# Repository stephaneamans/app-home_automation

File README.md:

# Home automation

## General principle

The general principle is based on a centralised ECU (Raspbery Pi) with an optional coprpocessor (STM32) used to manage low speed IO.
It shall communicate with satellite modules dedicated to specific tasks (like input, output and so on).

The main ECU shall communicate with an high speed link (Ethernet / WiFi) to the gateway.
A communication link shall be established with the satellite modules even by wire (RS-485) or wireless (NRF24L01, 2.4 gHz link).

The system is based on a Home Assistant server able to centralize different variables (temperature, lightining, ...),
commands (switch light on or off, enable a swimming pool filter, ...) or video streams (IP camera).
This server allows the system administrator to manage the system with a local computer and
users to interact with it through terminals (smartphone based, iOS or Android).

[Rapberry pi motherboard documentation](./01-raspberry_pi_motherboard/01-documentation/raspberry_pi_motherboard.md)

[Satellite module documentation](./02-module_satellite/01-documentation/module.md)

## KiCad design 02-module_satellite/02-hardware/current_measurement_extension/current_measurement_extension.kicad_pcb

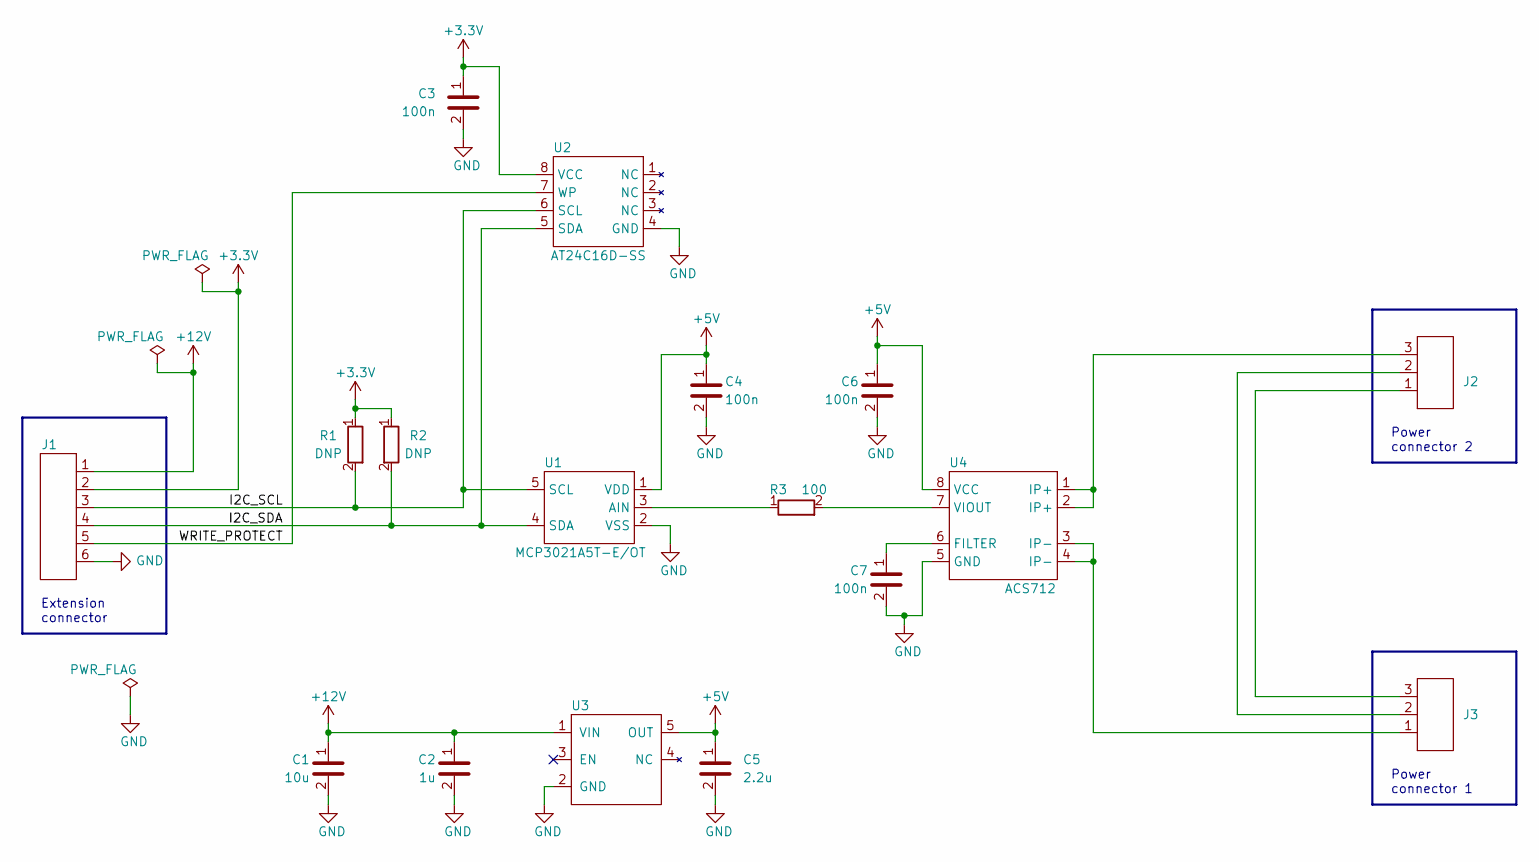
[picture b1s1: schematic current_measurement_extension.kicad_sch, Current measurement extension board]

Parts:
C1: 10u; C_1206_3216Metric_Pad1.33x1.80mm_HandSolder
C2: 1u; C_0603_1608Metric_Pad1.08x0.95mm_HandSolder
C3, C4, C6, C7: 100n; C_0603_1608Metric_Pad1.08x0.95mm_HandSolder
C5: 2.2u; C_0603_1608Metric_Pad1.08x0.95mm_HandSolder
J1: Conn_HE13_1x6_2.54V; PinHeader_1x06_P2.54mm_Vertical
J2, J3: Conn_HE13_1x3_2.54V; PinHeader_1x03_P2.54mm_Vertical
R1, R2: DNP; R_0603_1608Metric_Pad0.98x0.95mm_HandSolder
R3: 100; R_0603_1608Metric_Pad0.98x0.95mm_HandSolder
U1: MCP3021A5T-E/OT; SOT-23-5
U2: AT24C16D-SS; SOIC-8_3.9x4.9mm_P1.27mm
U3: TPS70950DBV; SOT-23-5
U4: ACS712; SOIC-8_3.9x4.9mm_P1.27mm

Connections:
+3.3V: C3.1, J1.2, R1.1, R2.1, U2.8 (VCC)
+5V: C4.1, C5.1, C6.1, U1.1 (VDD), U3.5 (OUT), U4.8 (VCC)
+12V: C1.1, C2.1, J1.1, U3.1 (VIN)
/I2C_SCL: J1.3, R1.2, U1.5 (SCL), U2.6 (SCL)
/I2C_SDA: J1.4, R2.2, U1.4 (SDA), U2.5 (SDA)
/WRITE_PROTECT: J1.5, U2.7 (WP)
GND: C1.2, C2.2, C3.2, C4.2, C5.2, C6.2, C7.2, J1.6, U1.2 (VSS), U2.4 (GND), U3.2 (GND), U4.5 (GND)
unnamed: J2.1, J3.3
unnamed: J2.2, J3.2
unnamed: J2.3, U4.1 (IP+), U4.2 (IP+)
unnamed: J3.1, U4.3 (IP-), U4.4 (IP-)
unnamed: R3.1, U1.3 (AIN)
unnamed: C7.1, U4.6 (FILTER)
unnamed: R3.2, U4.7 (VIOUT)

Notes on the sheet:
Power connector 1
Power connector 2
Extension connector

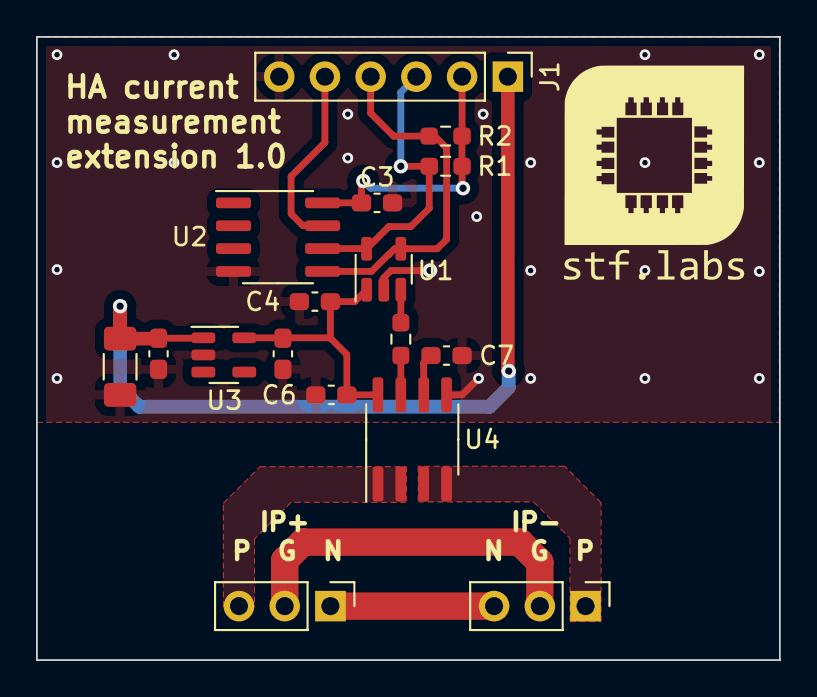
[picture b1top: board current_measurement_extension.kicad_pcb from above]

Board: 2 copper layers, 41.3 x 34.6 mm, 18 parts (0 on the bottom side), 14 nets.

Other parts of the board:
G1: LOGO; stf_labs_10mm

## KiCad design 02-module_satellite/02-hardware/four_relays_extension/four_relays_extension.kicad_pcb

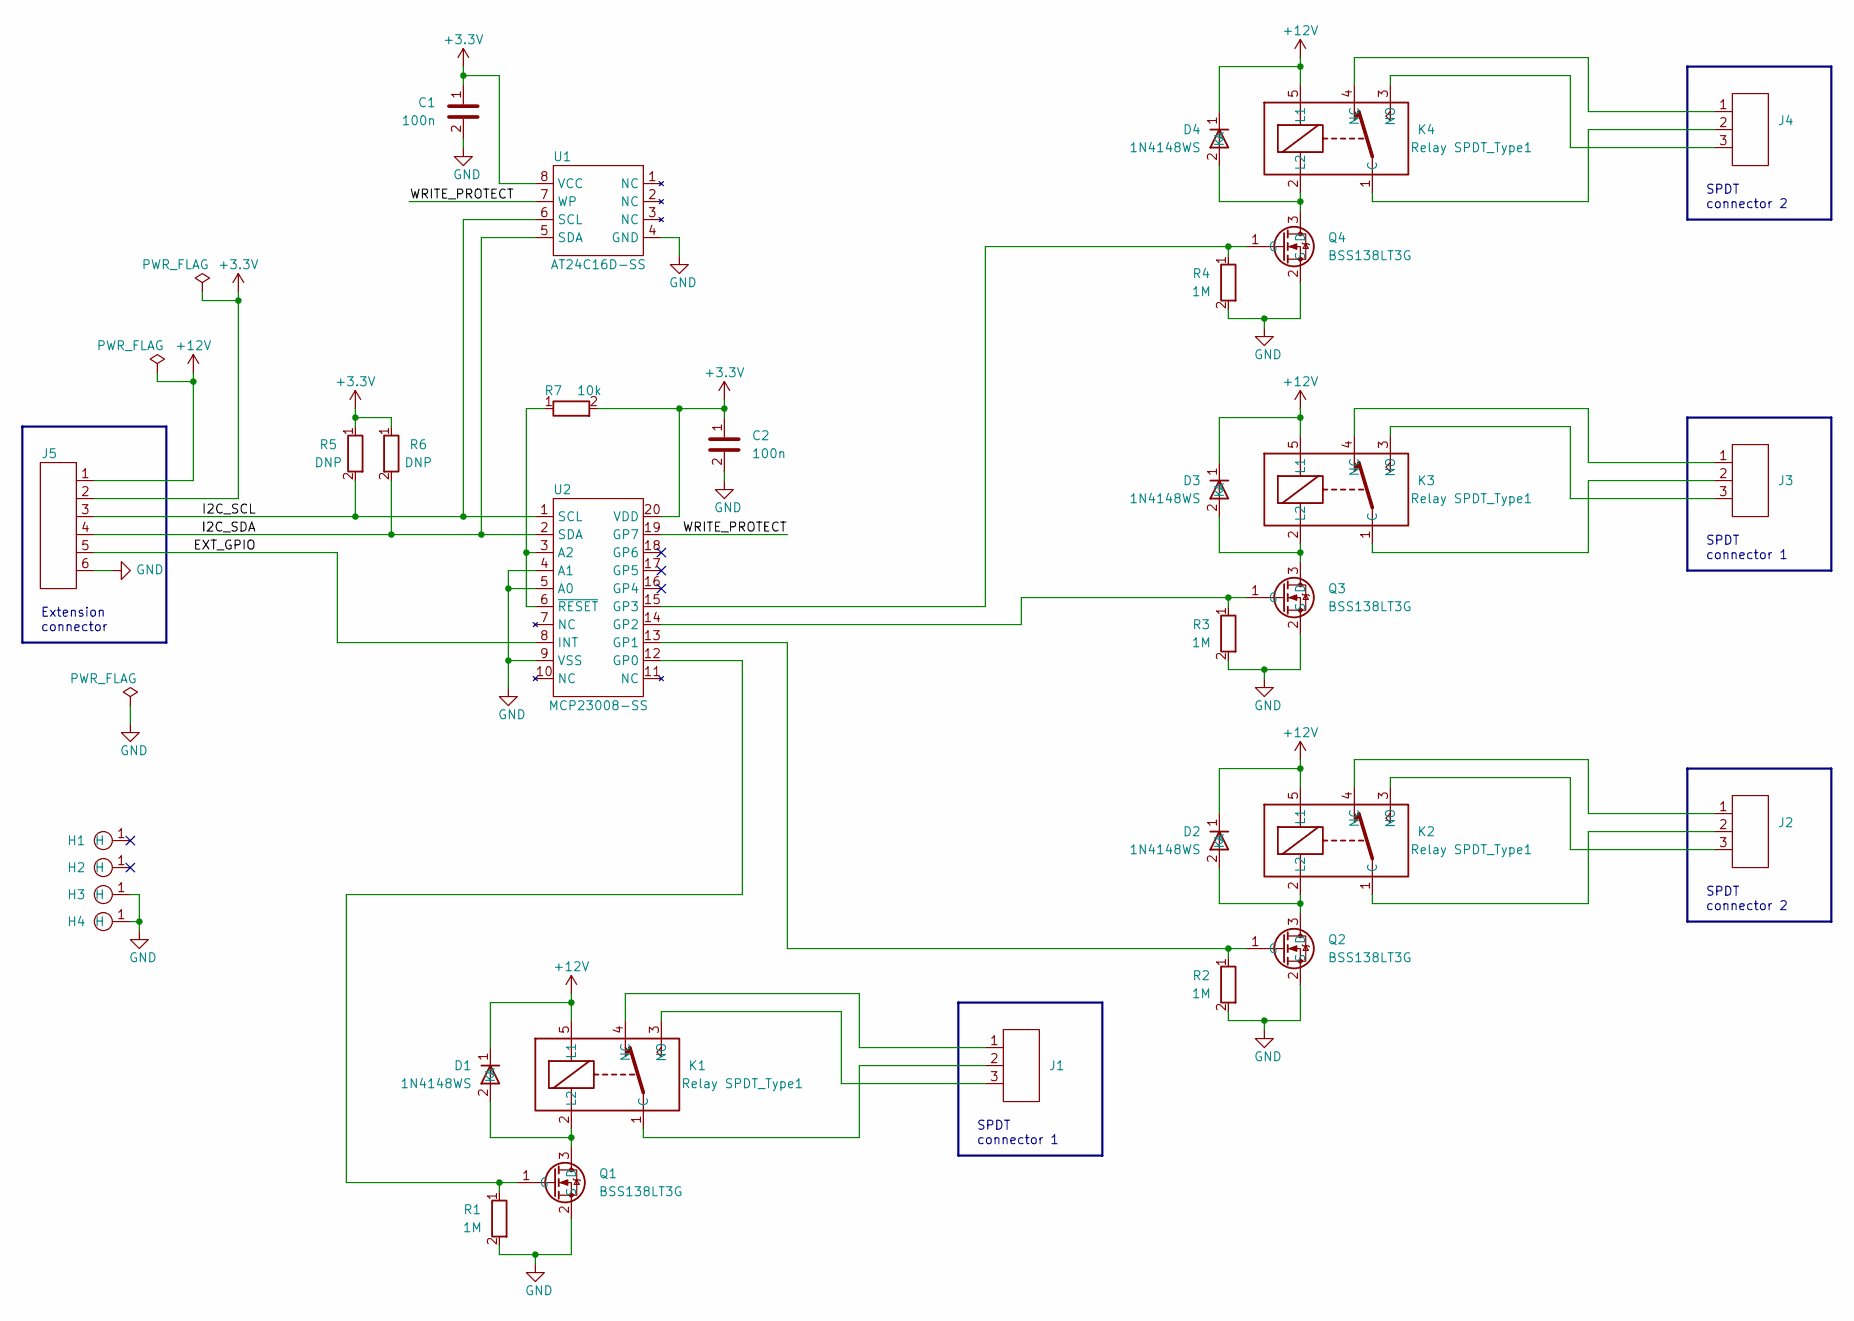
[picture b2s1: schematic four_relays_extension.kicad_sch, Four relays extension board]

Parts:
C1, C2: 100n; C_0603_1608Metric_Pad1.08x0.95mm_HandSolder
D1, D2, D3, D4: 1N4148WS; D_SOD-323_HandSoldering
H1, H2, H3, H4: drill_hole_5mm; Drill_hole_5mm
J1, J2, J3, J4: Conn_HE13_1x3_2.54V; PinHeader_1x03_P2.54mm_Vertical
J5: Conn_HE13_1x6_2.54V; PinHeader_1x06_P2.54mm_Vertical
K1, K2, K3, K4: Relay SPDT_Type1; Relay_SPDT_Type1
Q1, Q2, Q3, Q4: BSS138LT3G; SOT-23
R1, R2, R3, R4: 1M; R_0603_1608Metric_Pad0.98x0.95mm_HandSolder
R5, R6: DNP; R_0603_1608Metric_Pad0.98x0.95mm_HandSolder
R7: 10k; R_0603_1608Metric_Pad0.98x0.95mm_HandSolder
U1: AT24C16D-SS; SOIC-8_3.9x4.9mm_P1.27mm
U2: MCP23008-SS; SSOP-20_5.3x7.2mm_P0.65mm

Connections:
+3.3V: C1.1, C2.1, J5.2, R5.1, R6.1, R7.2, U1.8 (VCC), U2.20 (VDD)
+12V: D1.1 (K), D2.1 (K), D3.1 (K), D4.1 (K), J5.1, K1.5 (L1), K2.5 (L1), K3.5 (L1), K4.5 (L1)
/EXT_GPIO: J5.5, U2.8 (INT)
/I2C_SCL: J5.3, R5.2, U1.6 (SCL), U2.1 (SCL)
/I2C_SDA: J5.4, R6.2, U1.5 (SDA), U2.2 (SDA)
/WRITE_PROTECT: U1.7 (WP), U2.19 (GP7)
GND: C1.2, C2.2, H3.1 (H), H4.1 (H), J5.6, Q1.2 (S), Q2.2 (S), Q3.2 (S), Q4.2 (S), R1.2, R2.2, R3.2, R4.2, U1.4 (GND), U2.4 (A1), U2.5 (A0), U2.9 (VSS)
unnamed: D1.2 (A), K1.2 (L2), Q1.3 (D)
unnamed: D2.2 (A), K2.2 (L2), Q2.3 (D)
unnamed: D3.2 (A), K3.2 (L2), Q3.3 (D)
unnamed: D4.2 (A), K4.2 (L2), Q4.3 (D)
unnamed: J1.2, K1.1 (C)
unnamed: J1.1, K1.4 (NC)
unnamed: J1.3, K1.3 (NO)
unnamed: J2.2, K2.1 (C)
unnamed: J2.1, K2.4 (NC)
unnamed: J2.3, K2.3 (NO)
unnamed: J3.2, K3.1 (C)
unnamed: J3.1, K3.4 (NC)
unnamed: J3.3, K3.3 (NO)
unnamed: J4.2, K4.1 (C)
unnamed: J4.1, K4.4 (NC)
unnamed: J4.3, K4.3 (NO)
unnamed: Q1.1 (G), R1.1, U2.12 (GP0)
unnamed: Q2.1 (G), R2.1, U2.13 (GP1)
unnamed: Q3.1 (G), R3.1, U2.14 (GP2)
unnamed: Q4.1 (G), R4.1, U2.15 (GP3)
unnamed: R7.1, U2.3 (A2), U2.6 (~RESET)

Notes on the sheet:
SPDT connector 2
SPDT connector 1
Extension connector

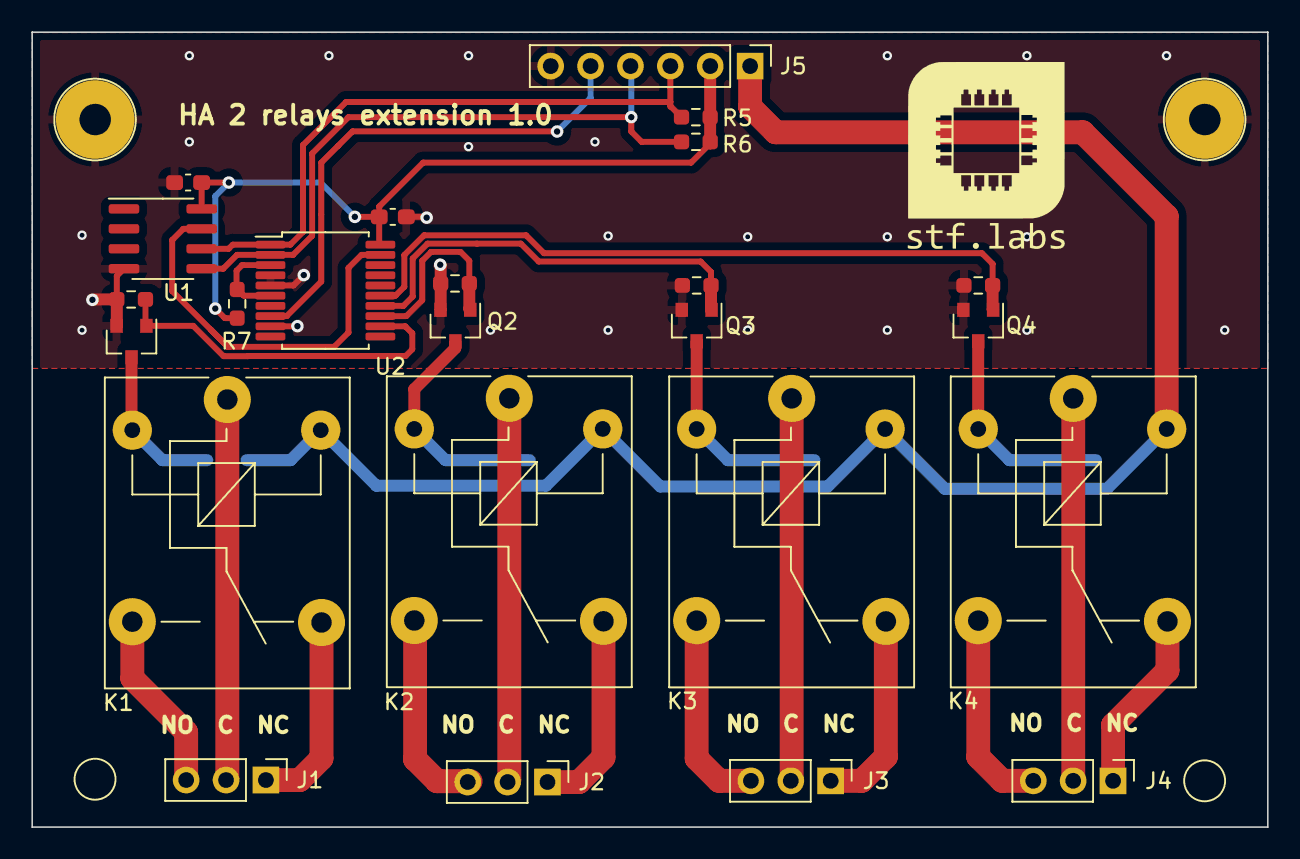
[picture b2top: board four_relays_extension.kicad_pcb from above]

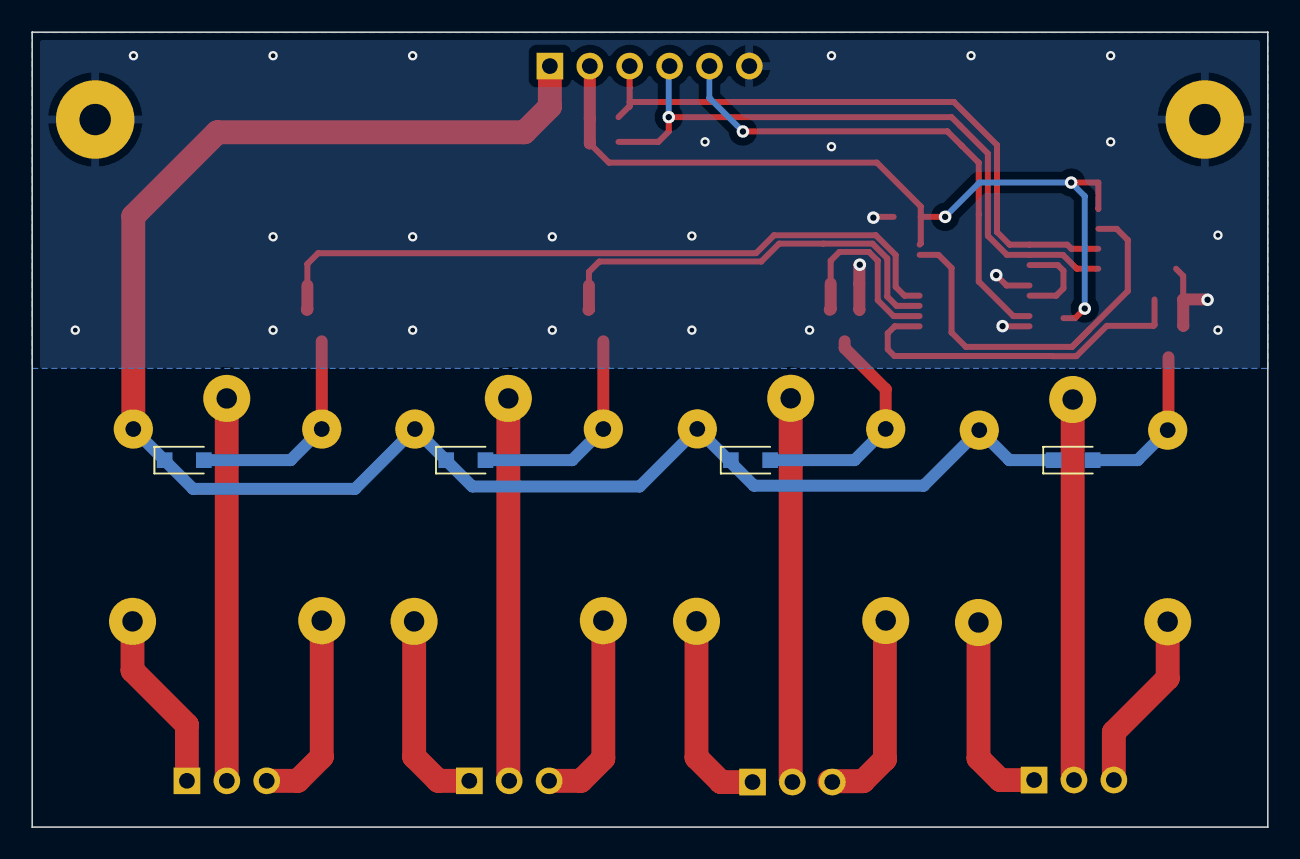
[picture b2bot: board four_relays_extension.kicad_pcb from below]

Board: 2 copper layers, 78.7 x 50.6 mm, 33 parts (4 on the bottom side), 28 nets.

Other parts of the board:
G1: LOGO; stf_labs_10mm

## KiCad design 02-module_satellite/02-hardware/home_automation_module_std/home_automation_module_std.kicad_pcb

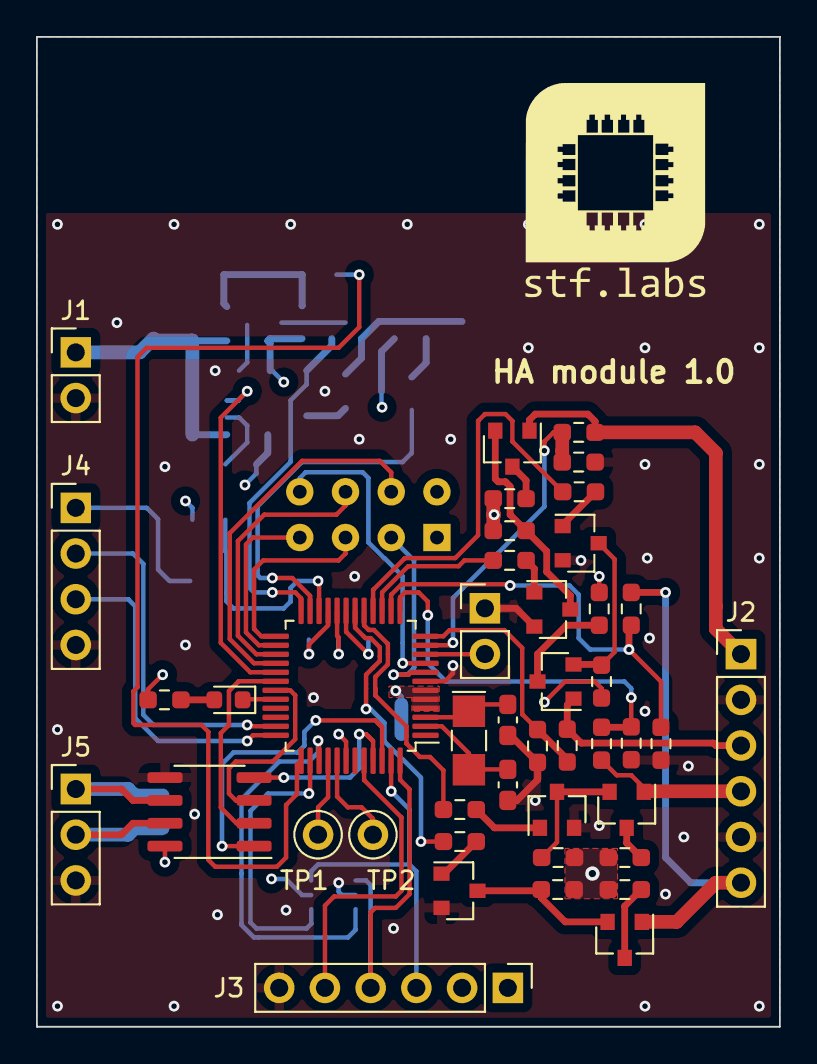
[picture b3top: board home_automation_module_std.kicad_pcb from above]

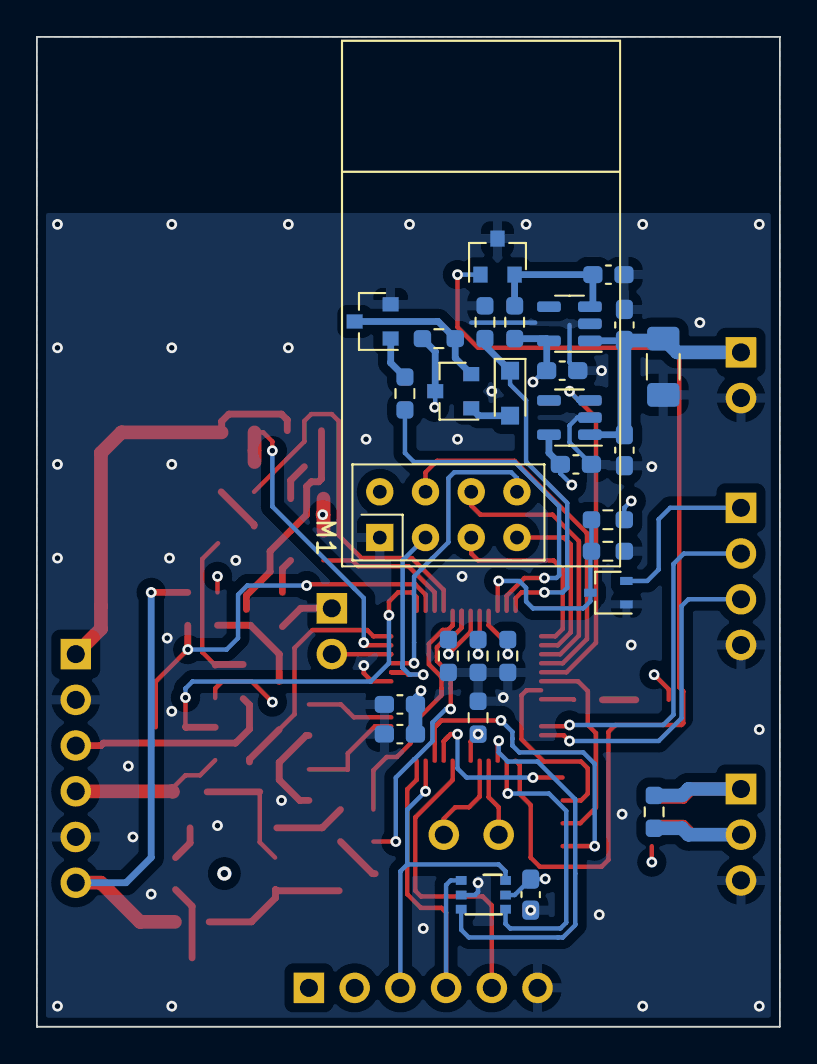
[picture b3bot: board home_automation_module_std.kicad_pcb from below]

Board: 4 copper layers, 41.3 x 55.0 mm, 73 parts (29 on the bottom side), 67 nets.

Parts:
C1, C4, C7, C11: 1u; C_0603_1608Metric_Pad1.08x0.95mm_HandSolder
C2, C5: 2.2u; C_0603_1608Metric_Pad1.08x0.95mm_HandSolder
C3: 10u; C_1206_3216Metric_Pad1.33x1.80mm_HandSolder
C6, C8: 100n; C_0603_1608Metric_Pad1.08x0.95mm_HandSolder
C9, C10: TBD; C_0603_1608Metric_Pad1.08x0.95mm_HandSolder
D1: SFH5701_A01; D_SOD-323_HandSoldering
D2: LED_G; LED_0603_1608Metric
D3: BAT54SW; SOT-323
G1: LOGO; stf_labs_10mm
J1, J6: Conn_HE13_1x2_2.54V; PinHeader_1x02_P2.54mm_Vertical
J2, J3: Conn_HE13_1x6_2.54V; PinHeader_1x06_P2.54mm_Vertical
J4: Conn_HE13_1x4_2.54V; PinHeader_1x04_P2.54mm_Vertical
J5: Conn_HE13_1x3_2.54V; PinHeader_1x03_P2.54mm_Vertical
M1: nRF24L01; nRF24L01_Breakout
Q1, Q3, Q5, Q7, Q9: BSS315PH6327XTSA1; SOT-23
Q2, Q4, Q6, Q8, Q10: BC848B; SOT-23
Q11: 2SK1829; SOT-23
R1, R5, R6, R9, R10, R14, R15, R19, R20, R31: 10k; R_0603_1608Metric_Pad0.98x0.95mm_HandSolder
R2, R7, R12, R17, R22: 1k; R_0603_1608Metric_Pad0.98x0.95mm_HandSolder
R3: 3.3k; R_0603_1608Metric_Pad0.98x0.95mm_HandSolder
R4, R26, R27, R28, R29: DNP; R_0603_1608Metric_Pad0.98x0.95mm_HandSolder
R8, R13, R18, R23: 390k; R_0603_1608Metric_Pad0.98x0.95mm_HandSolder
R11, R16, R21, R24: 120k; R_0603_1608Metric_Pad0.98x0.95mm_HandSolder
R30: 330; R_0603_1608Metric_Pad0.98x0.95mm_HandSolder
R32: 15k; R_0603_1608Metric_Pad0.98x0.95mm_HandSolder
R33: 4.7k; R_0603_1608Metric_Pad0.98x0.95mm_HandSolder
TP1, TP2: test_point_th; TP_TH_2.54mm
U1: TPS70933DBV; SOT-23-5
U2: TPS70950DBV; SOT-23-5
U3: DFN-6-1EP_2.5x2.5mm_P0.65mm_EP2.45x1.55mm
U4: MAX487CSA_ESA; SOIC-8_3.9x4.9mm_P1.27mm
U5: STM32G030_C8; LQFP-48_7x7mm_P0.5mm
Y1: Crystal_3.2x1.5mm; Crystal_SMD_3.2x1.5mm

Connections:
+3.3V: C2.1, C6.1, C7.1, C8.1, D3.2 (K), J3.2, J4.1, M1.2 (VCC), Q1.3 (S), R1.1, R30.1, R31.2, U1.5 (OUT), U3.5 (VDD), U5.4 (VBAT), U5.5 (VREF+), U5.6 (VDD/VDDA)
+5V: C5.1, U2.5 (OUT), U4.8 (VCC)
+12V: C1.1, C3.1, C4.1, J1.1, J3.1, R5.1, R6.1, R9.1, R10.1, R14.1, R15.1, R19.1, R20.1, R32.2, U1.1 (VIN), U2.1 (VIN)
/3_3V_EN: C11.1, Q11.2 (D), R31.1, U1.3 (EN)
/5V_EN: U2.3 (EN), U5.29 (PA9)
/EXT_GPIO: J3.5, U5.44 (PB5)
/I2C_SCL: J3.3, U3.6 (SCL), U5.47 (PB8)
/I2C_SDA: J3.4, U3.1 (SDA), U5.48 (PB9)
/Input_stage/DRIVE_CMD1_EN: R7.2, U5.15 (PA4)
/Input_stage/DRIVE_CMD2_EN: R12.2, U5.16 (PA5)
/Input_stage/DRIVE_CMD3_EN: R17.2, U5.17 (PA6)
/Input_stage/DRIVE_CMD4_EN: R22.2, U5.18 (PA7)
/Input_stage/INPUT1: J2.1, Q3.1 (D), R8.1
/Input_stage/INPUT2: J2.3, Q5.1 (D), R13.1
/Input_stage/INPUT3: J2.4, Q7.1 (D), R18.1
/Input_stage/INPUT4: J2.6, Q9.1 (D), R23.1
/Input_stage/MCU_INPUT1: R8.2, R11.1, U5.11 (PA0)
/Input_stage/MCU_INPUT2: R13.2, R16.1, U5.12 (PA1)
/Input_stage/MCU_INPUT3: R18.2, R21.1, U5.13 (PA2)
/Input_stage/MCU_INPUT4: R23.2, R24.1, U5.14 (PA3)
/LIGHT_SENSOR_EN: R2.2, U5.23 (PB11)
/NRF24L01_CE: M1.3 (CE), U5.8 (PF0)
/NRF24L01_CS: M1.4 (SPI_CS), U5.28 (PA8)
/NRF24L01_IRQ: M1.8 (IRQ), U5.9 (PF1)
/SPI_MISO: M1.7 (SPI_MISO), U5.26 (PB14)
/SPI_MOSI: M1.6 (SPI_MOSI), U5.27 (PB15)
/SPI_SCK: M1.5 (SPI_SCK), U5.25 (PB13)
/SWD_CLK: J4.3, U5.36 (PA14)
/SWD_IO: J4.2, U5.35 (PA13)
/UART_RX: U4.1 (RO), U5.46 (PB7)
/UART_TX: U4.4 (DI), U5.45 (PB6)
/mcu/ADDR: U3.3 (ADD), U5.39 (PD1)
/mcu/AD_12V: D3.3 (A/K), R32.1, R33.2, U5.22 (PB10)
/mcu/AD_LIGHT: D1.1 (K), R3.1, U5.24 (PB12)
/mcu/DBG0: TP1.1 (TP), U5.40 (PD2)
/mcu/DBG1: TP2.1 (TP), U5.41 (PD3)
/mcu/HW_VERSION0: R26.1, U5.19 (PB0)
/mcu/HW_VERSION1: R27.1, U5.20 (PB1)
/mcu/HW_VERSION2: R28.1, U5.21 (PB2)
/mcu/HW_VERSION3: R29.1, U5.42 (PB3)
/mcu/MAX487_DE: U4.3 (DE), U5.31 (PC7)
/mcu/RTC_CLK_IN: C9.1, U5.2 (PC14), Y1.2
/mcu/RTC_CLK_OUT: C10.1, U5.3 (PC15), Y1.1
/mcu/~3_3V_EN: Q11.1 (G), U5.37 (PA15)
/mcu/~MAX487_RE: U4.2 (/RE), U5.30 (PC6)
/mcu/~NRST: J6.2, U5.10 (NRST)
/~RST: U3.4 (RST), U5.38 (PD0)
GND: C1.2, C2.2, C3.2, C4.2, C5.2, C6.2, C7.2, C8.2, C9.2, C10.2, C11.2, D3.1 (A), J1.2, J2.2, J2.5, J3.6, J4.4, J5.3, J6.1, M1.1 (GND), Q2.2 (E), Q4.2 (E), Q6.2 (E), Q8.2 (E), Q10.2 (E), Q11.3 (S), R3.2, R11.2, R16.2, R21.2, R24.2, R26.2, R27.2, R28.2, R29.2, R33.1, U1.2 (GND), U2.2 (GND), U3.2 (GND), U4.5 (GND), U5.7 (VSS/VSSA)
unnamed: D1.2 (A), Q1.1 (D)
unnamed: D2.2 (AR), R30.2
unnamed: D2.1 (KR), U5.32 (PA10)
unnamed: Q1.2 (G), Q2.3 (C), R1.2
unnamed: Q2.1 (B), R2.1
unnamed: Q3.2 (G), Q4.3 (C), R6.2
unnamed: Q3.3 (S), R5.2
unnamed: Q4.1 (B), R7.1
unnamed: Q5.2 (G), Q6.3 (C), R10.2
unnamed: Q5.3 (S), R9.2
unnamed: Q6.1 (B), R12.1
unnamed: Q7.2 (G), Q8.3 (C), R15.2
unnamed: Q7.3 (S), R14.2
unnamed: Q8.1 (B), R17.1
unnamed: Q9.3 (S), R19.2
unnamed: Q10.1 (B), R22.1
unnamed: Q9.2 (G), Q10.3 (C), R20.2
unnamed: J5.1, R4.1, U4.6 (A)
unnamed: J5.2, R4.2, U4.7 (B)

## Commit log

2023-12-24 [DOC] Start module global principle and HW architecture documentation
2023-12-24 update_project_tree
2023-12-24 documentation update
2023-12-24 hardware_schematic_wip
2024-01-04 Update doc
2024-01-04 doc Update
2024-03-24 [DOC] Update_project_tree
2024-03-24 [HW] Home automation module schematic v1.0
2024-03-24 [HW] Input stage simulation
2024-05-22 [HW] Home automation module PCB v1.0
2024-06-01 [HW] Home automation two relays extension schematic v1.0
2024-06-01 [HW] Home automation two relays extension PCB v1.0
2024-06-06 [HW] Home automation four relays extension schematic v1.0
2024-06-06 [HW] Home automation four relays extension PCB v1.0
2024-06-09 [HW] Home automation current measurement extension schematic v1.0
2024-06-09 [HW] Home automation current measurement extension PCB v1.0
